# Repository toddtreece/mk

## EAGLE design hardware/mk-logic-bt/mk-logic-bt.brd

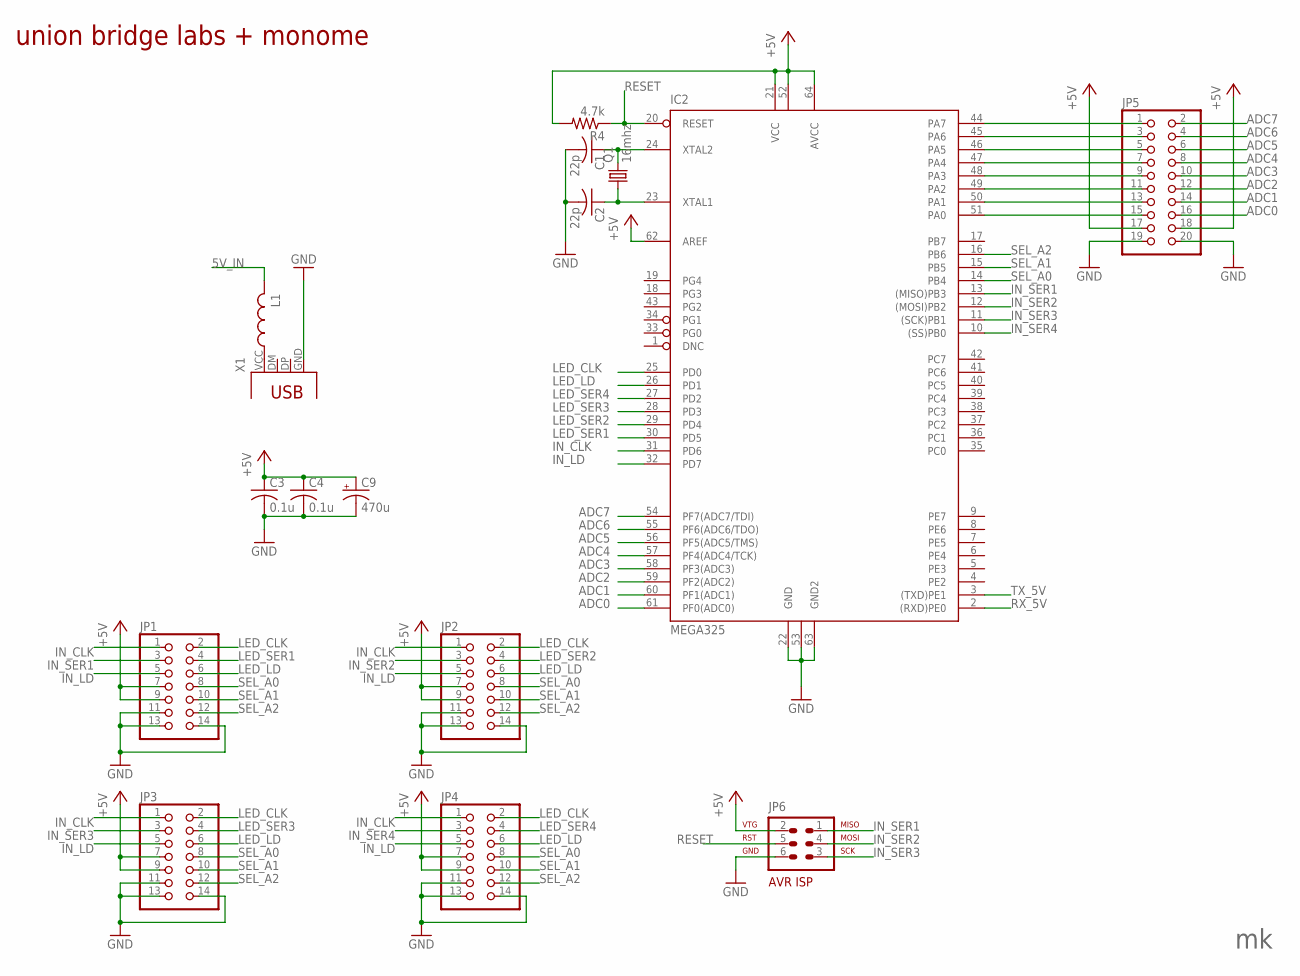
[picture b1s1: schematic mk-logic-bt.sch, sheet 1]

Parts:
C1, C2: 22p; C1206
C3, C4: 0.1u; C1206
C9: 470u; PANASONIC_E
IC2: MEGA325; TQFP64
JP1, JP2, JP3, JP4: PINHD-2X7; 2X07
JP5: PINHD-2X10; 2X10
JP6: AVR-ISP; AVR-ISP-6
L1: L-USL3216C; L3216C
Q1: 16mhz; HC49UP
R4: 4.7k; R1206
X1: USB_TYPE_B; USB_B

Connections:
5V_IN: L1.2; also elsewhere on the board
+5V: C3.1, C4.1, C9.+, IC2.21 (VCC), IC2.52 (VCC1), IC2.62 (AREF), IC2.64 (AVCC), JP1.7, JP1.9, JP2.7, JP2.9, JP3.7, JP3.9, JP4.7, JP4.9, JP5.17, JP5.18, JP6.2, R4.2; also elsewhere on the board
ADC0: IC2.61 (PF0(ADC0)), JP5.16
ADC1: IC2.60 (PF1(ADC1)), JP5.14
ADC2: IC2.59 (PF2(ADC2)), JP5.12
ADC3: IC2.58 (PF3(ADC3)), JP5.10
ADC4: IC2.57 (PF4(ADC4/TCK)), JP5.8
ADC5: IC2.56 (PF5(ADC5/TMS)), JP5.6
ADC6: IC2.55 (PF6(ADC6/TDO)), JP5.4
ADC7: IC2.54 (PF7(ADC7/TDI)), JP5.2
GND: C1.2, C2.2, C3.2, C4.2, C9.-, IC2.22 (GND), IC2.53 (GND1), IC2.63 (GND2), JP1.11, JP1.13, JP1.14, JP2.11, JP2.13, JP2.14, JP3.11, JP3.13, JP3.14, JP4.11, JP4.13, JP4.14, JP5.19, JP5.20, JP6.6, X1.GND; also elsewhere on the board
IN_CLK: IC2.31 (PD6), JP1.1, JP2.1, JP3.1, JP4.1
IN_LD: IC2.32 (PD7), JP1.5, JP2.5, JP3.5, JP4.5
IN_SER1: IC2.13 ((MISO)PB3), JP1.3, JP6.1
IN_SER2: IC2.12 ((MOSI)PB2), JP2.3, JP6.4
IN_SER3: IC2.11 ((SCK)PB1), JP3.3, JP6.3
IN_SER4: IC2.10 ((SS)PB0), JP4.3
LED_CLK: IC2.25 (PD0), JP1.2, JP2.2, JP3.2, JP4.2
LED_LD: IC2.26 (PD1), JP1.6, JP2.6, JP3.6, JP4.6
LED_SER1: IC2.30 (PD5), JP1.4
LED_SER2: IC2.29 (PD4), JP2.4
LED_SER3: IC2.28 (PD3), JP3.4
LED_SER4: IC2.27 (PD2), JP4.4
unnamed: IC2.44 (PA7), JP5.1
unnamed: IC2.45 (PA6), JP5.3
unnamed: IC2.46 (PA5), JP5.5
unnamed: IC2.47 (PA4), JP5.7
unnamed: C2.1, IC2.23 (XTAL1), Q1.1
unnamed: C1.1, IC2.24 (XTAL2), Q1.2
unnamed: IC2.48 (PA3), JP5.9
unnamed: IC2.49 (PA2), JP5.11
unnamed: L1.1, X1.VCC
unnamed: IC2.50 (PA1), JP5.13
unnamed: IC2.51 (PA0), JP5.15
RESET: IC2.20 (RESET), JP6.5, R4.1
RX_5V: IC2.2 ((RXD)PE0); also elsewhere on the board
SEL_A0: IC2.14 (PB4), JP1.8, JP2.8, JP3.8, JP4.8
SEL_A1: IC2.15 (PB5), JP1.10, JP2.10, JP3.10, JP4.10
SEL_A2: IC2.16 (PB6), JP1.12, JP2.12, JP3.12, JP4.12
TX_5V: IC2.3 ((TXD)PE1); also elsewhere on the board

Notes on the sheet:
union bridge labs + monome

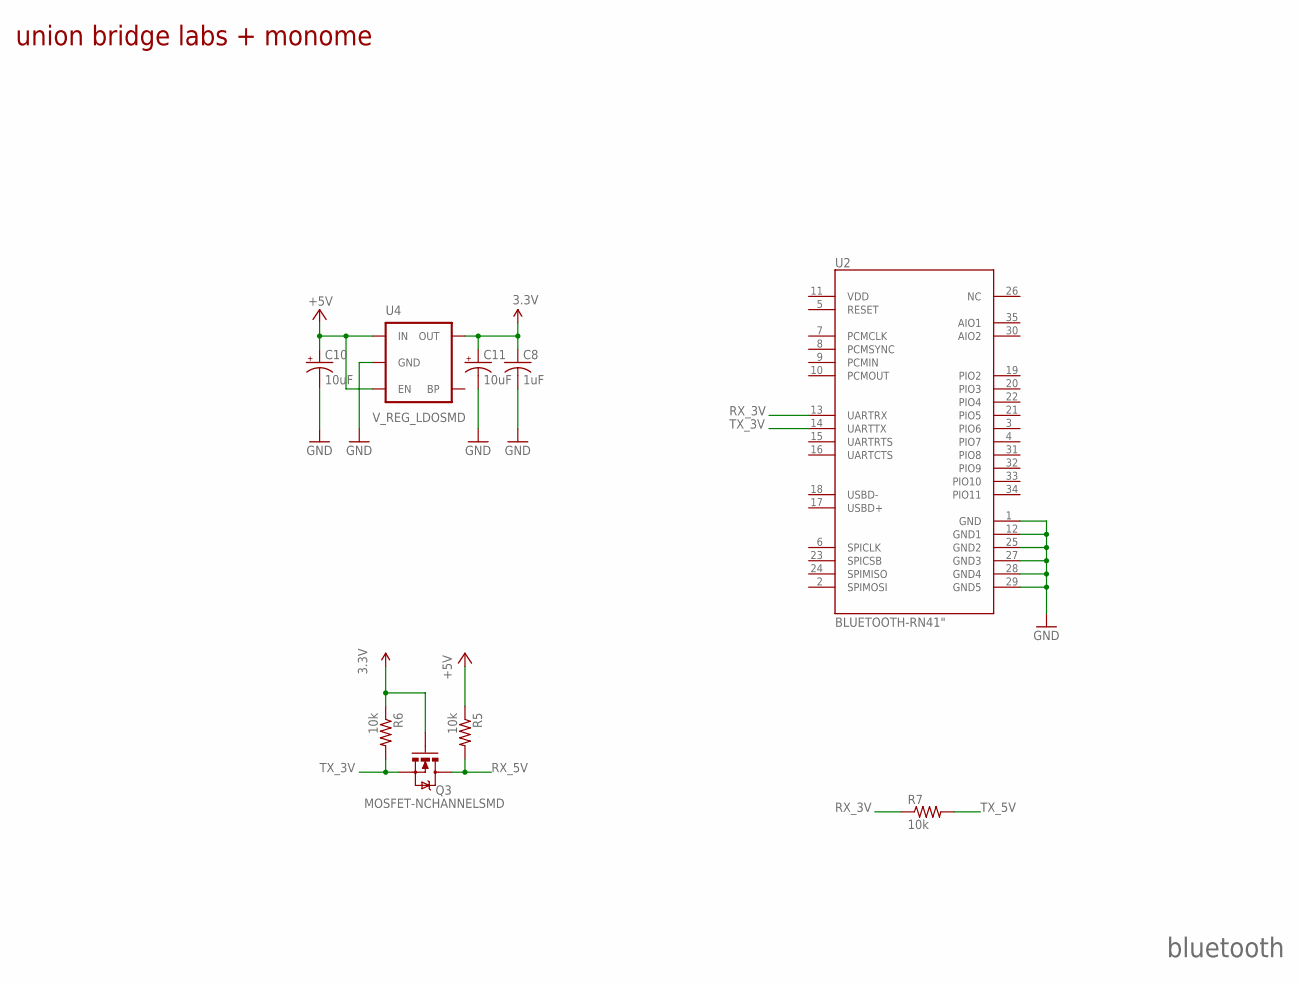
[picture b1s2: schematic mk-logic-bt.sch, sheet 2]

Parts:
C8: 1uF; C1206
C10, C11: 10uF; EIA3216
Q3: MOSFET-NCHANNELSMD; SOT23-3
R5, R6, R7: 10k; R1206
U2: BLUETOOTH-RN41"; RN41
U4: V_REG_LDOSMD; SOT23-5

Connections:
3.3V: C8.1, C11.A (+), Q3.1 (G), R6.1, U4.5 (OUT)
+5V: C10.A (+), R5.1, U4.1 (IN), U4.3 (EN); also elsewhere on the board
GND: C8.2, C10.C (-), C11.C (-), U2.1 (GND), U2.12 (GND1), U2.25 (GND2), U2.27 (GND3), U2.28 (GND4), U2.29 (GND5), U4.2 (GND); also elsewhere on the board
RX_3V: R7.1, U2.13 (UARTRX)
RX_5V: Q3.3 (D), R5.2; also elsewhere on the board
TX_3V: Q3.2 (S), R6.2, U2.14 (UARTTX)
TX_5V: R7.2; also elsewhere on the board

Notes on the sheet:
union bridge labs + monome
bluetooth

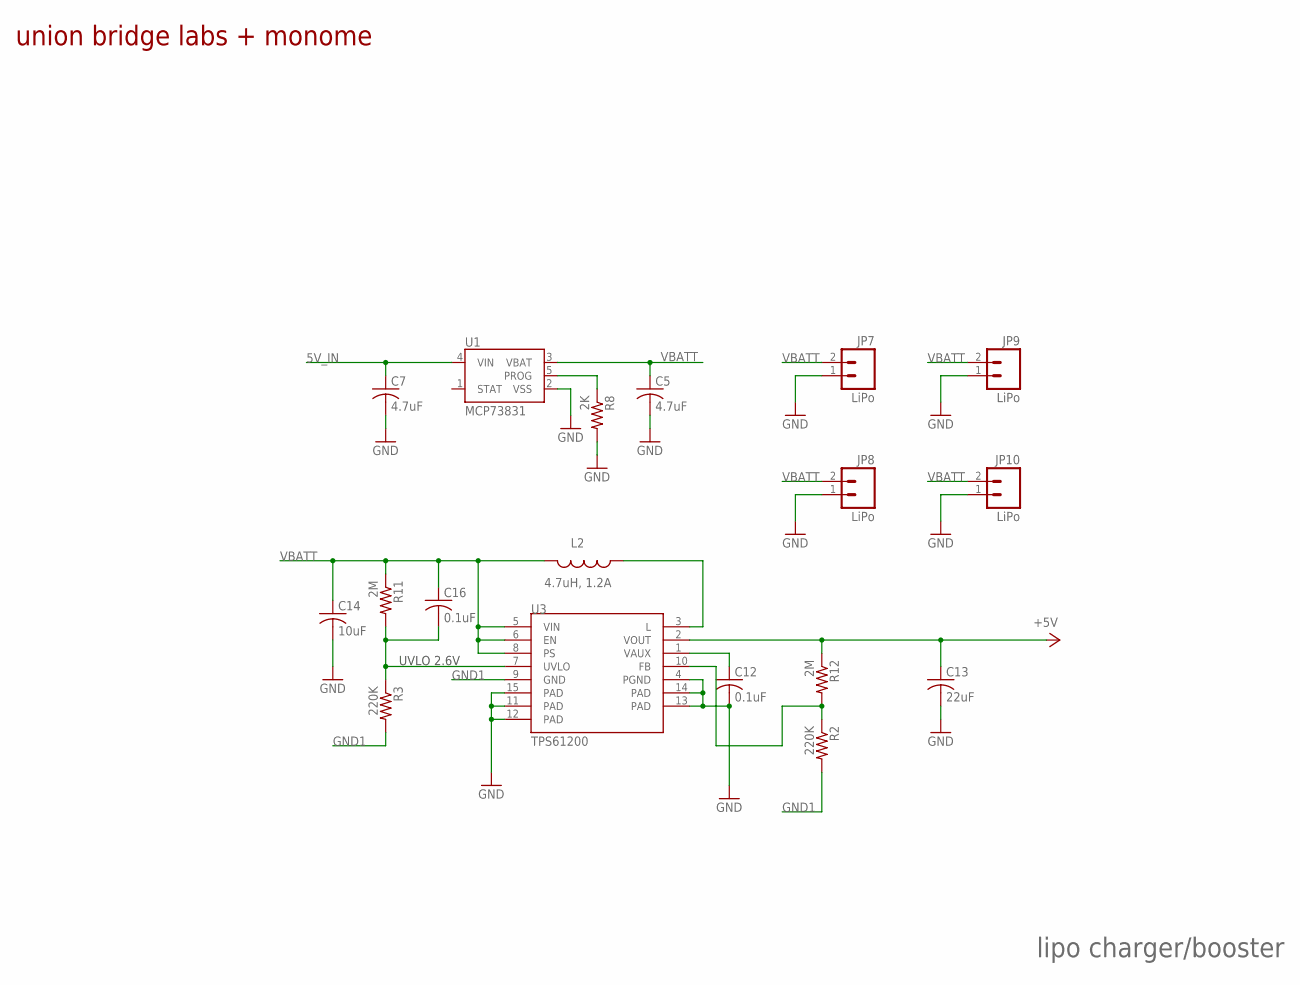
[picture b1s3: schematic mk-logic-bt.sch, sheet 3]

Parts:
C5, C7: 4.7uF; C1206
C12, C16: 0.1uF; C1206
C13: 22uF; C1206
C14: 10uF; C1206
JP7, JP8, JP9, JP10: LiPo; JST-2-SMD
L2: 4.7uH, 1.2A; CDRH2D09
R2, R3: 220K; R1206
R8: 2K; R1206
R11, R12: 2M; R1206
U1: MCP73831; SOT23-5
U3: TPS61200; QFN-10_PAD

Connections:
5V_IN: C7.1, U1.4 (VIN); also elsewhere on the board
+5V: C13.1, R12.1, U3.2 (VOUT); also elsewhere on the board
GND: C5.2, C7.2, C12.2, C13.2, C14.2, JP7.1, JP8.1, JP9.1, JP10.1, R8.2, U1.2 (VSS), U3.4 (PGND), U3.11 (PAD), U3.12 (PAD), U3.13 (PAD), U3.14 (PAD), U3.15 (PAD); also elsewhere on the board
GND1: R2.2, R3.2, U3.9 (GND)
unnamed: R8.1, U1.5 (PROG)
unnamed: L2.P$1 (1), U3.3 (L)
unnamed: C12.1, U3.1 (VAUX)
unnamed: R2.1, R12.2, U3.10 (FB)
UVLO: C16.2, R3.1, R11.2, U3.7 (UVLO)
VBATT: C5.1, C14.1, C16.1, JP7.2, JP8.2, JP9.2, JP10.2, L2.P$2 (2), R11.1, U1.3 (VBAT), U3.5 (VIN), U3.6 (EN), U3.8 (PS)

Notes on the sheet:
union bridge labs + monome
lipo charger/booster
UVLO 2.6V

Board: 2 copper layers, 45 parts (0 on the bottom side), 50 nets, no tracks yet.

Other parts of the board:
U6, U7: FEDUCIAL

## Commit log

2011-12-10 Start of monome bluetooth firmware mods
2011-12-12 start of attiny 2313 parallel <--> serial
2011-12-28 initialize timer0
2011-12-31 Abandoning add-on board
2012-01-02 finished mk bluetooth schematic
    TODO: layout board & route traces

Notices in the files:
parts and their libraries:
SparkFun: Licensing: CC v3.0 Share-Alike You are welcome to use this library for commercial purposes.
